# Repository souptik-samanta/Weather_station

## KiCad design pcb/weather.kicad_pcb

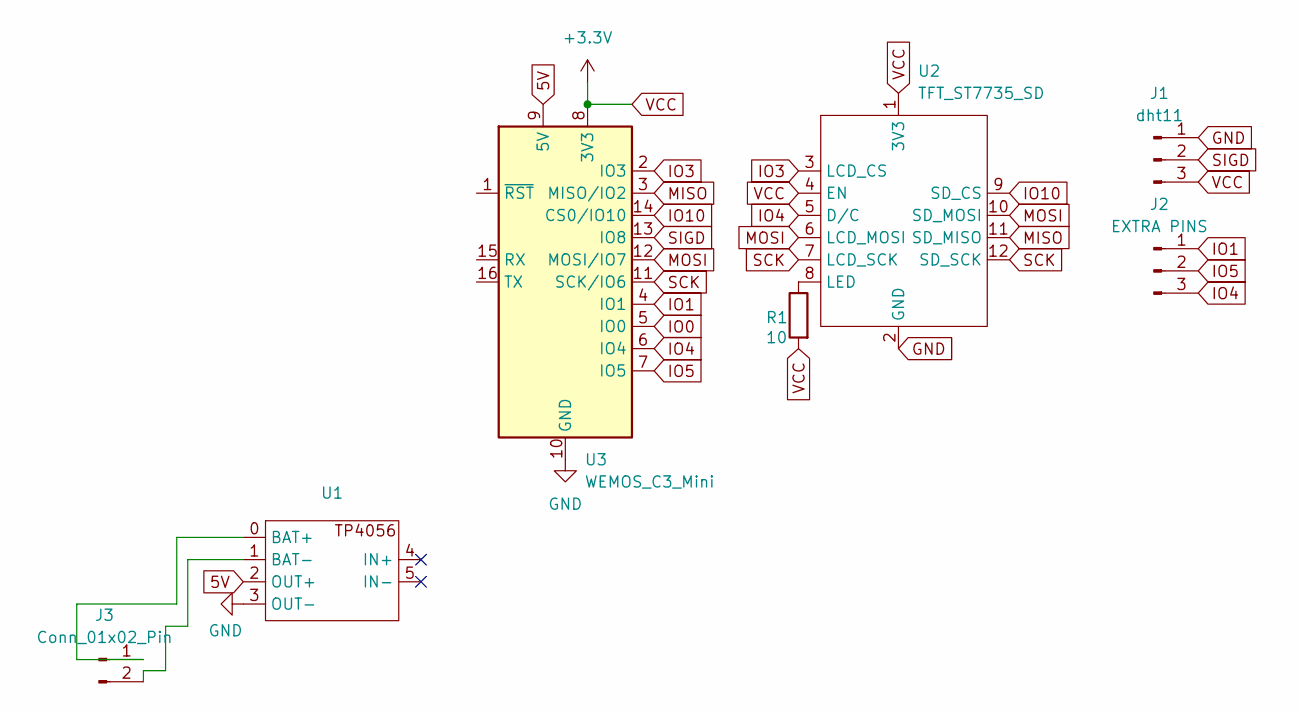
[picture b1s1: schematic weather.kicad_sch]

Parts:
J1: dht11; PinHeader_1x03_P2.54mm_Vertical
J2: EXTRA PINS; PinHeader_1x03_P2.54mm_Vertical
J3: Conn_01x02_Pin; PinHeader_1x02_P2.00mm_Vertical
R1: 10; R_Axial_DIN0204_L3.6mm_D1.6mm_P5.08mm_Horizontal
U1: TP4056
U2: TFT_ST7735_SD
U3: WEMOS_C3_Mini; WEMOS_C3_mini

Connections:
5V: U1.2 (OUT+), U3.9 (5V)
GND: J1.1, U1.3 (OUT-), U2.2 (GND), U3.10 (GND)
IO0: U3.5 (IO0)
IO1: J2.1, U3.4 (IO1)
IO3: U2.3 (LCD_CS), U3.2 (IO3)
IO4: J2.3, U2.5 (D/C), U3.6 (IO4)
IO5: J2.2, U3.7 (IO5)
IO10: U2.9 (SD_CS), U3.14 (CS0/IO10)
MISO: U2.11 (SD_MISO), U3.3 (MISO/IO2)
MOSI: U2.6 (LCD_MOSI), U2.10 (SD_MOSI), U3.12 (MOSI/IO7)
unnamed: J3.1, U1.0 (BAT+)
unnamed: J3.2, U1.1 (BAT-)
unnamed: R1.2, U2.8 (LED)
SCK: U2.7 (LCD_SCK), U2.12 (SD_SCK), U3.11 (SCK/IO6)
SIGD: J1.2, U3.13 (IO8)
VCC: J1.3, R1.1, U2.1 (3V3), U2.4 (EN), U3.8 (3V3)

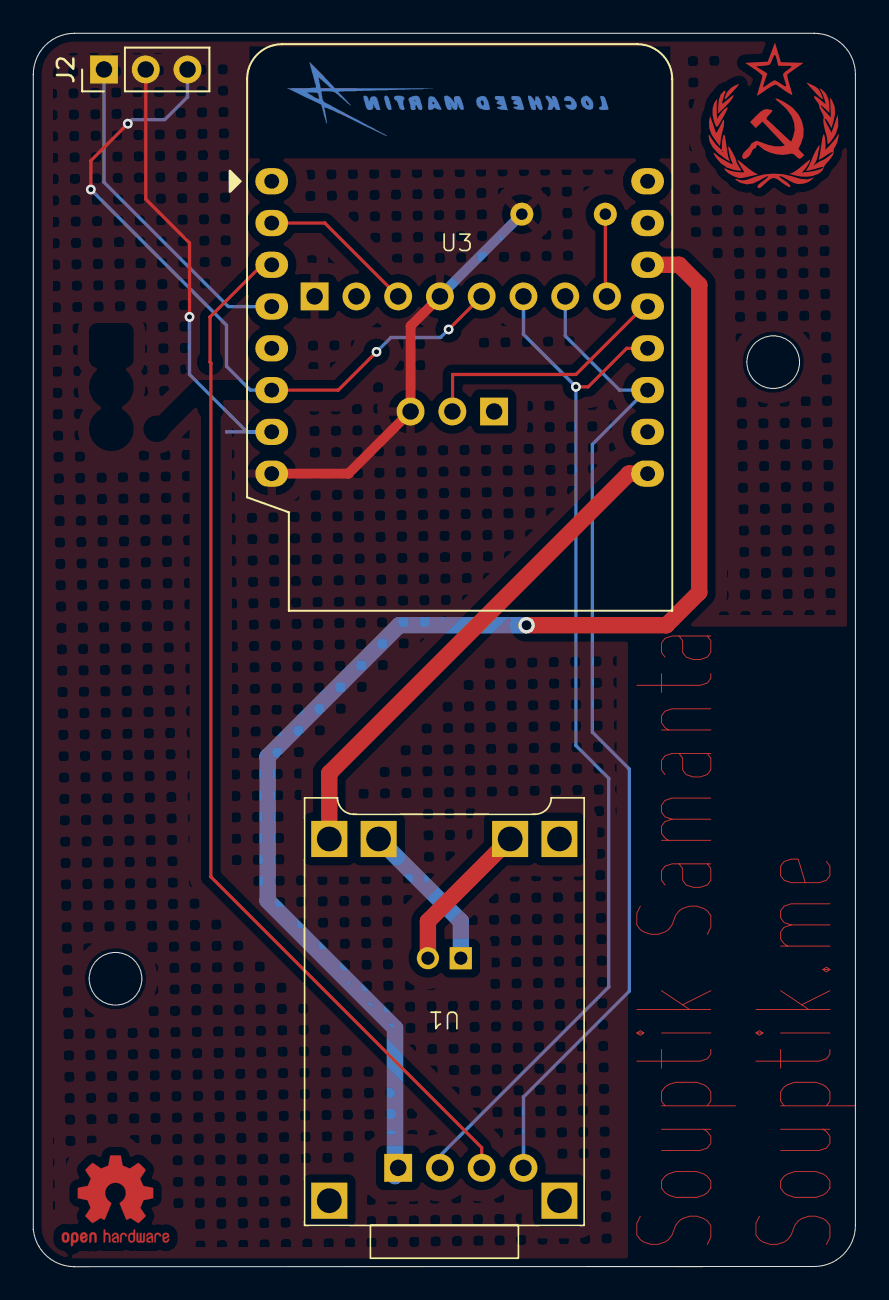
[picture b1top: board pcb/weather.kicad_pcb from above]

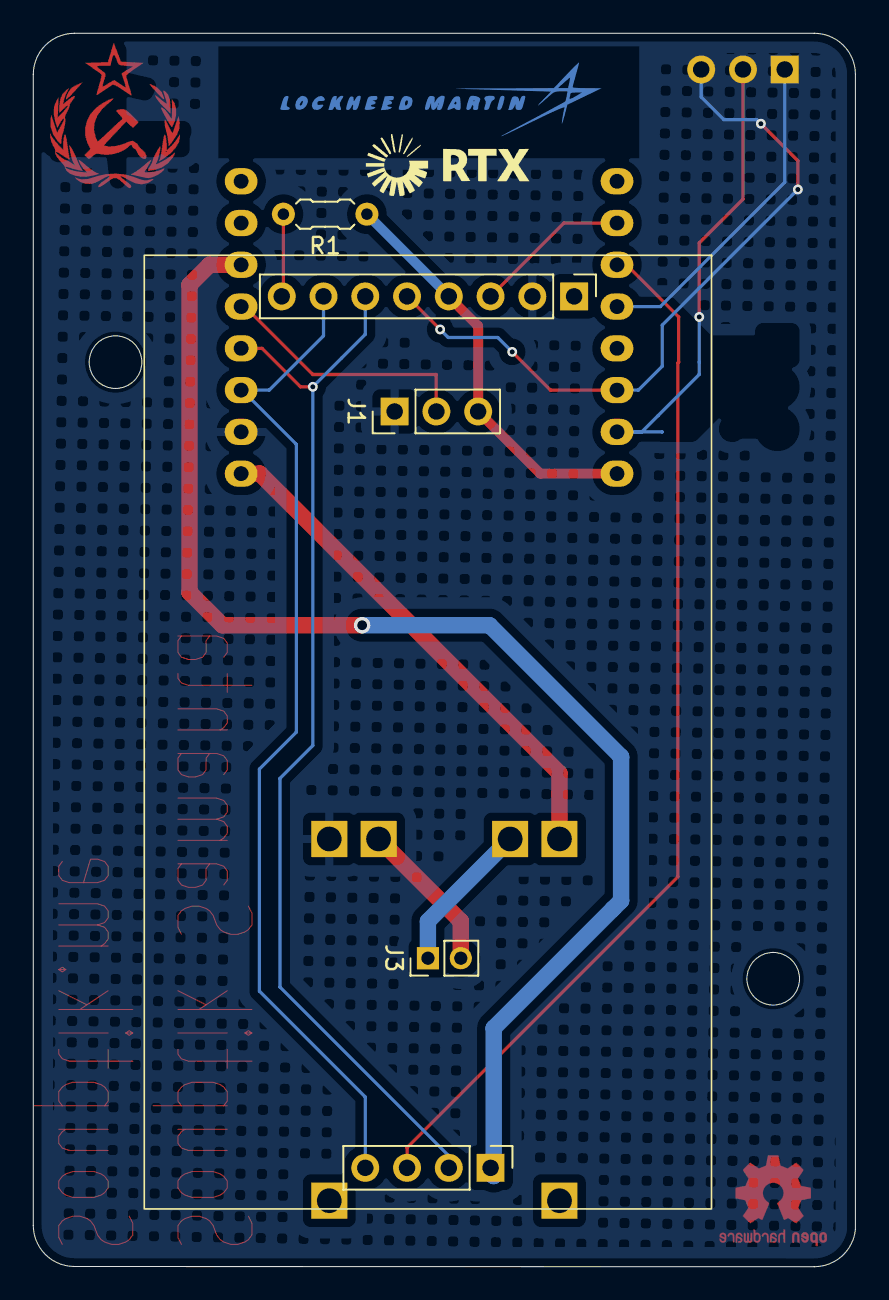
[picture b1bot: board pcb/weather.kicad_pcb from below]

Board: 2 copper layers, 50.0 x 75.0 mm, 7 parts (4 on the bottom side), 15 nets.

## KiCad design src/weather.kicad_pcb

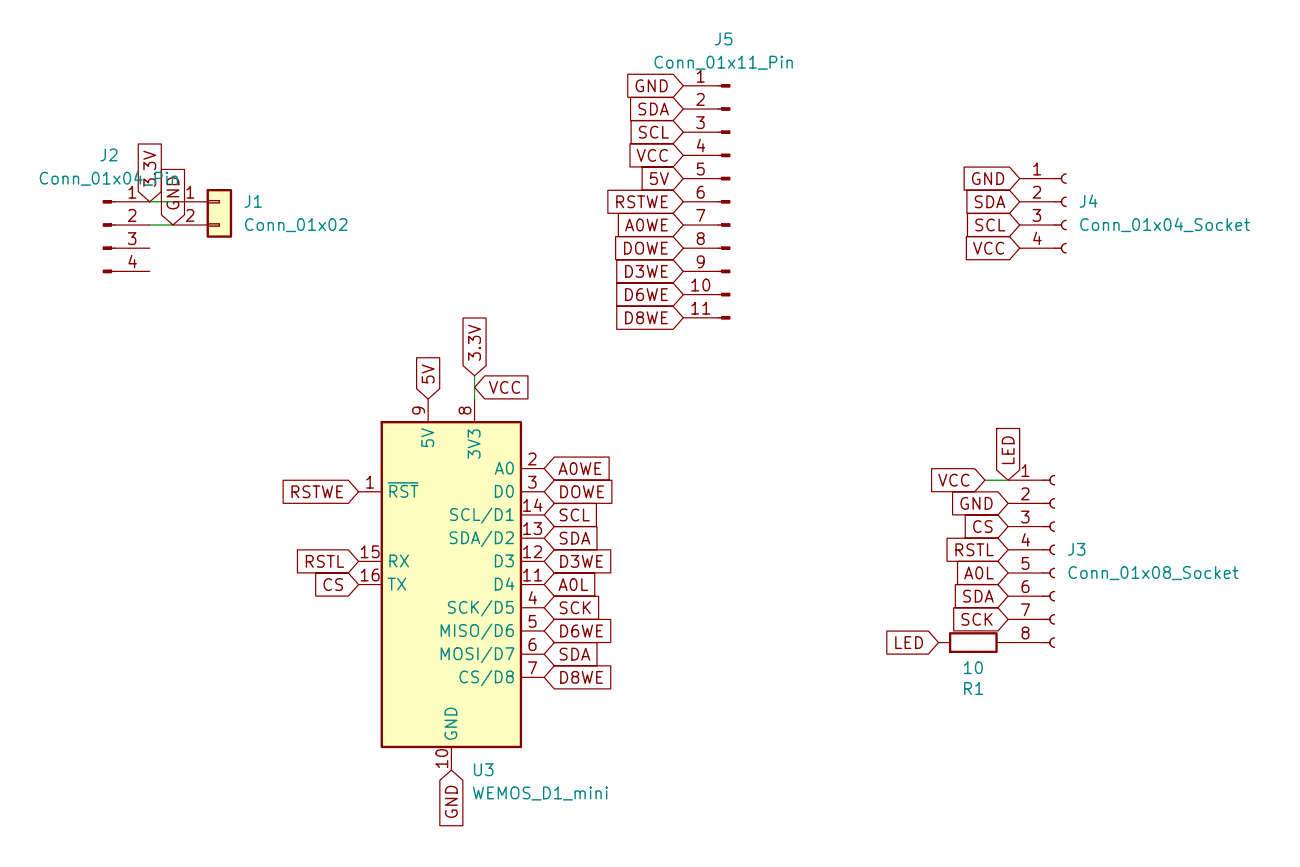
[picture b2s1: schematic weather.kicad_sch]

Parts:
J1: Conn_01x02; PinHeader_1x02_P2.54mm_Vertical
J2: Conn_01x04_Pin; PinHeader_1x04_P2.54mm_Vertical
J3: Conn_01x08_Socket; PinHeader_1x08_P2.54mm_Vertical
J4: Conn_01x04_Socket; PinHeader_1x04_P2.54mm_Vertical
J5: Conn_01x11_Pin; PinHeader_1x11_P2.54mm_Vertical
R1: 10; R_0805_2012Metric
U3: WEMOS_D1_mini; WEMOS_D1_mini_light

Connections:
3.3V: J1.1, J2.1, J3.1, J4.4, J5.4, R1.1, U3.8 (3V3)
5V: J5.5, U3.9 (5V)
A0L: J3.5, U3.11 (D4)
A0WE: J5.7, U3.2 (A0)
CS: J3.3, U3.16 (TX)
D3WE: J5.9, U3.12 (D3)
D6WE: J5.10, U3.5 (MISO/D6)
D8WE: J5.11, U3.7 (CS/D8)
DOWE: J5.8, U3.3 (D0)
GND: J1.2, J2.2, J3.2, J4.1, J5.1, U3.10 (GND)
unnamed: J3.8, R1.2
RSTL: J3.4, U3.15 (RX)
RSTWE: J5.6, U3.1 (~RST)
SCK: J3.7, U3.4 (SCK/D5)
SCL: J4.3, J5.3, U3.14 (SCL/D1)
SDA: J3.6, J4.2, J5.2, U3.6 (MOSI/D7), U3.13 (SDA/D2)

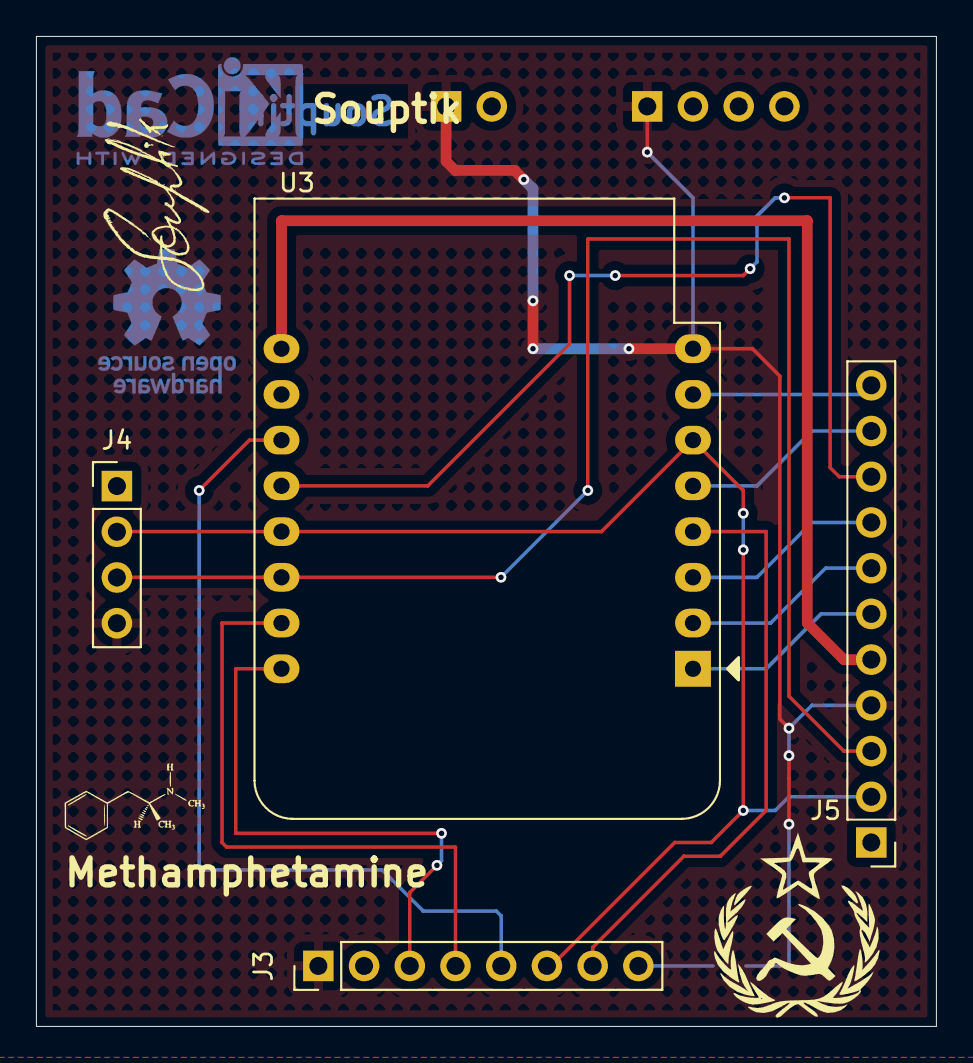
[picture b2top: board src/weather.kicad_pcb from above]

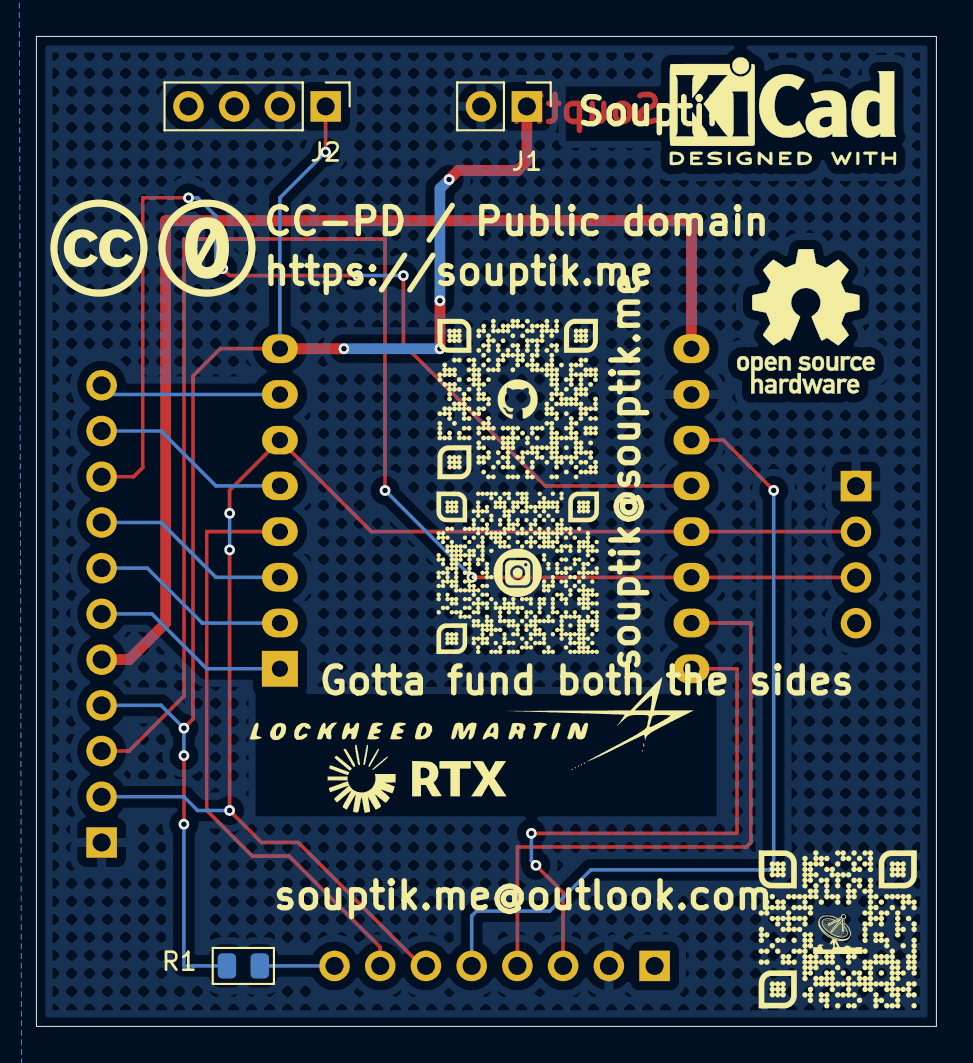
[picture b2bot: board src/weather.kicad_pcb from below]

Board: 2 copper layers, 50.0 x 55.0 mm, 7 parts (3 on the bottom side), 16 nets.

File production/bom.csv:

Designator,Footprint,Quantity,Value,LCSC Part #
J1,PinHeader_1x02_P2.54mm_Vertical,1,Conn_01x02,
J2,PinHeader_1x04_P2.54mm_Vertical,1,Conn_01x04_Pin,
J3,PinHeader_1x08_P2.54mm_Vertical,1,Conn_01x08_Socket,
J4,PinHeader_1x04_P2.54mm_Vertical,1,Conn_01x04_Socket,
J5,PinHeader_1x11_P2.54mm_Vertical,1,Conn_01x11_Pin,
R1,0805,1,10,
U3,WEMOS_D1_mini_light,1,WEMOS_D1_mini,

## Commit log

2025-01-29 1st u
2025-04-17 pcb did

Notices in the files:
parts and their libraries:
CC-PD / Public domain
